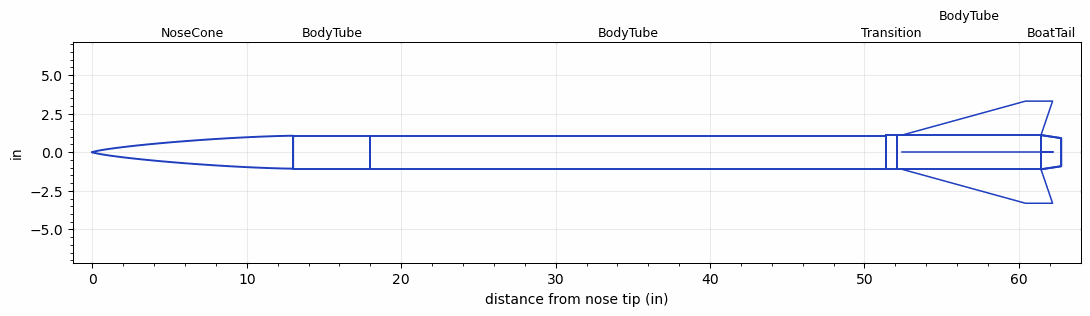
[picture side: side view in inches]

<RASAeroDocument>
 <FileVersion>2</FileVersion>
 <RocketDesign>
  <NoseCone>
   <Length>13</Length>
   <Diameter>2.13</Diameter>
   <Shape>Von Karman Ogive</Shape>
   <BluntRadius>0.08</BluntRadius>
   <Location>0</Location>
  </NoseCone>
  <BodyTube>
   <Length>5</Length>
   <Diameter>2.13</Diameter>
   <Location>13</Location>
  </BodyTube>
  <BodyTube>
   <Length>33.38</Length>
   <Diameter>2.13</Diameter>
   <Location>18</Location>
  </BodyTube>
  <Transition>
   <Length>0.75</Length>
   <Diameter>2.215</Diameter>
   <Location>51.38</Location>
   <RearDiameter>2.215</RearDiameter>
  </Transition>
  <BodyTube>
   <Length>9.3</Length>
   <Diameter>2.215</Diameter>
   <Location>52.13</Location>
   <BoattailLength>1.305</BoattailLength>
   <BoattailRearDiameter>1.82</BoattailRearDiameter>
   <Fin>
    <Count>4</Count>
    <Chord>9</Chord>
    <Span>2.2</Span>
    <SweepDistance>8</SweepDistance>
    <TipChord>1.75</TipChord>
    <Thickness>0.15</Thickness>
    <LERadius>0.05</LERadius>
    <Location>9</Location>
    <AirfoilSection>Double Wedge</AirfoilSection>
    <FX1>3</FX1>
    <FX3>0.34</FX3>
   </Fin>
  </BodyTube>
  <BoatTail>
   <Length>1.305</Length>
   <Diameter>2.215</Diameter>
   <RearDiameter>1.82</RearDiameter>
   <Location>61.43</Location>
  </BoatTail>
  <Surface>Smooth Paint</Surface>
  <ModifiedBarrowman>True</ModifiedBarrowman>
  <Turbulence>True</Turbulence>
  <UseBooster1>False</UseBooster1>
  <UseBooster2>False</UseBooster2>
 </RocketDesign>
 <LaunchSite>
  <Altitude>4000</Altitude>
  <Pressure>25.85</Pressure>
  <RodAngle>2</RodAngle>
  <RodLength>96</RodLength>
  <Temperature>70</Temperature>
  <WindSpeed>4.47</WindSpeed>
 </LaunchSite>
 <Recovery>
  <Altitude1>0</Altitude1>
  <Altitude2>0</Altitude2>
  <DeviceType1>None</DeviceType1>
  <DeviceType2>None</DeviceType2>
  <Event1>False</Event1>
  <Event2>False</Event2>
  <Size1>0</Size1>
  <Size2>0</Size2>
  <EventType1>None</EventType1>
  <EventType2>None</EventType2>
  <CD1>0</CD1>
  <CD2>0</CD2>
 </Recovery>
 <SimulationList>
  <Simulation>
   <SustainerEngine>M1378LR  (Loki)</SustainerEngine>
   <SustainerLaunchWt>11.79</SustainerLaunchWt>
   <SustainerNozzleDiameter>1.58</SustainerNozzleDiameter>
   <SustainerCG>37.9</SustainerCG>
   <SustainerIgnitionDelay>0</SustainerIgnitionDelay>
   <Booster1SeparationDelay>0</Booster1SeparationDelay>
   <Booster1IgnitionDelay>0</Booster1IgnitionDelay>
   <IncludeBooster1>False</IncludeBooster1>
   <Booster2Delay>0</Booster2Delay>
   <IncludeBooster2>False</IncludeBooster2>
   <TimetoApogee>59.636</TimetoApogee>
   <MaxAltitude>73460.92</MaxAltitude>
   <MaxVelocity>3814.417</MaxVelocity>
   <OptimumWt>9.684859</OptimumWt>
   <OptimumMaxAlt>9.684859</OptimumMaxAlt>
  </Simulation>
  <Simulation>
   <SustainerLaunchWt>5.0676</SustainerLaunchWt>
   <SustainerCG>43.8171</SustainerCG>
   <SustainerIgnitionDelay>0</SustainerIgnitionDelay>
   <Booster1SeparationDelay>0</Booster1SeparationDelay>
   <Booster1IgnitionDelay>0</Booster1IgnitionDelay>
   <IncludeBooster1>False</IncludeBooster1>
   <Booster2Delay>0</Booster2Delay>
   <IncludeBooster2>False</IncludeBooster2>
  </Simulation>
 </SimulationList>
</RASAeroDocument>
